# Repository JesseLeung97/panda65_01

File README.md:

# panda65_01
Kicad files for panda65_01

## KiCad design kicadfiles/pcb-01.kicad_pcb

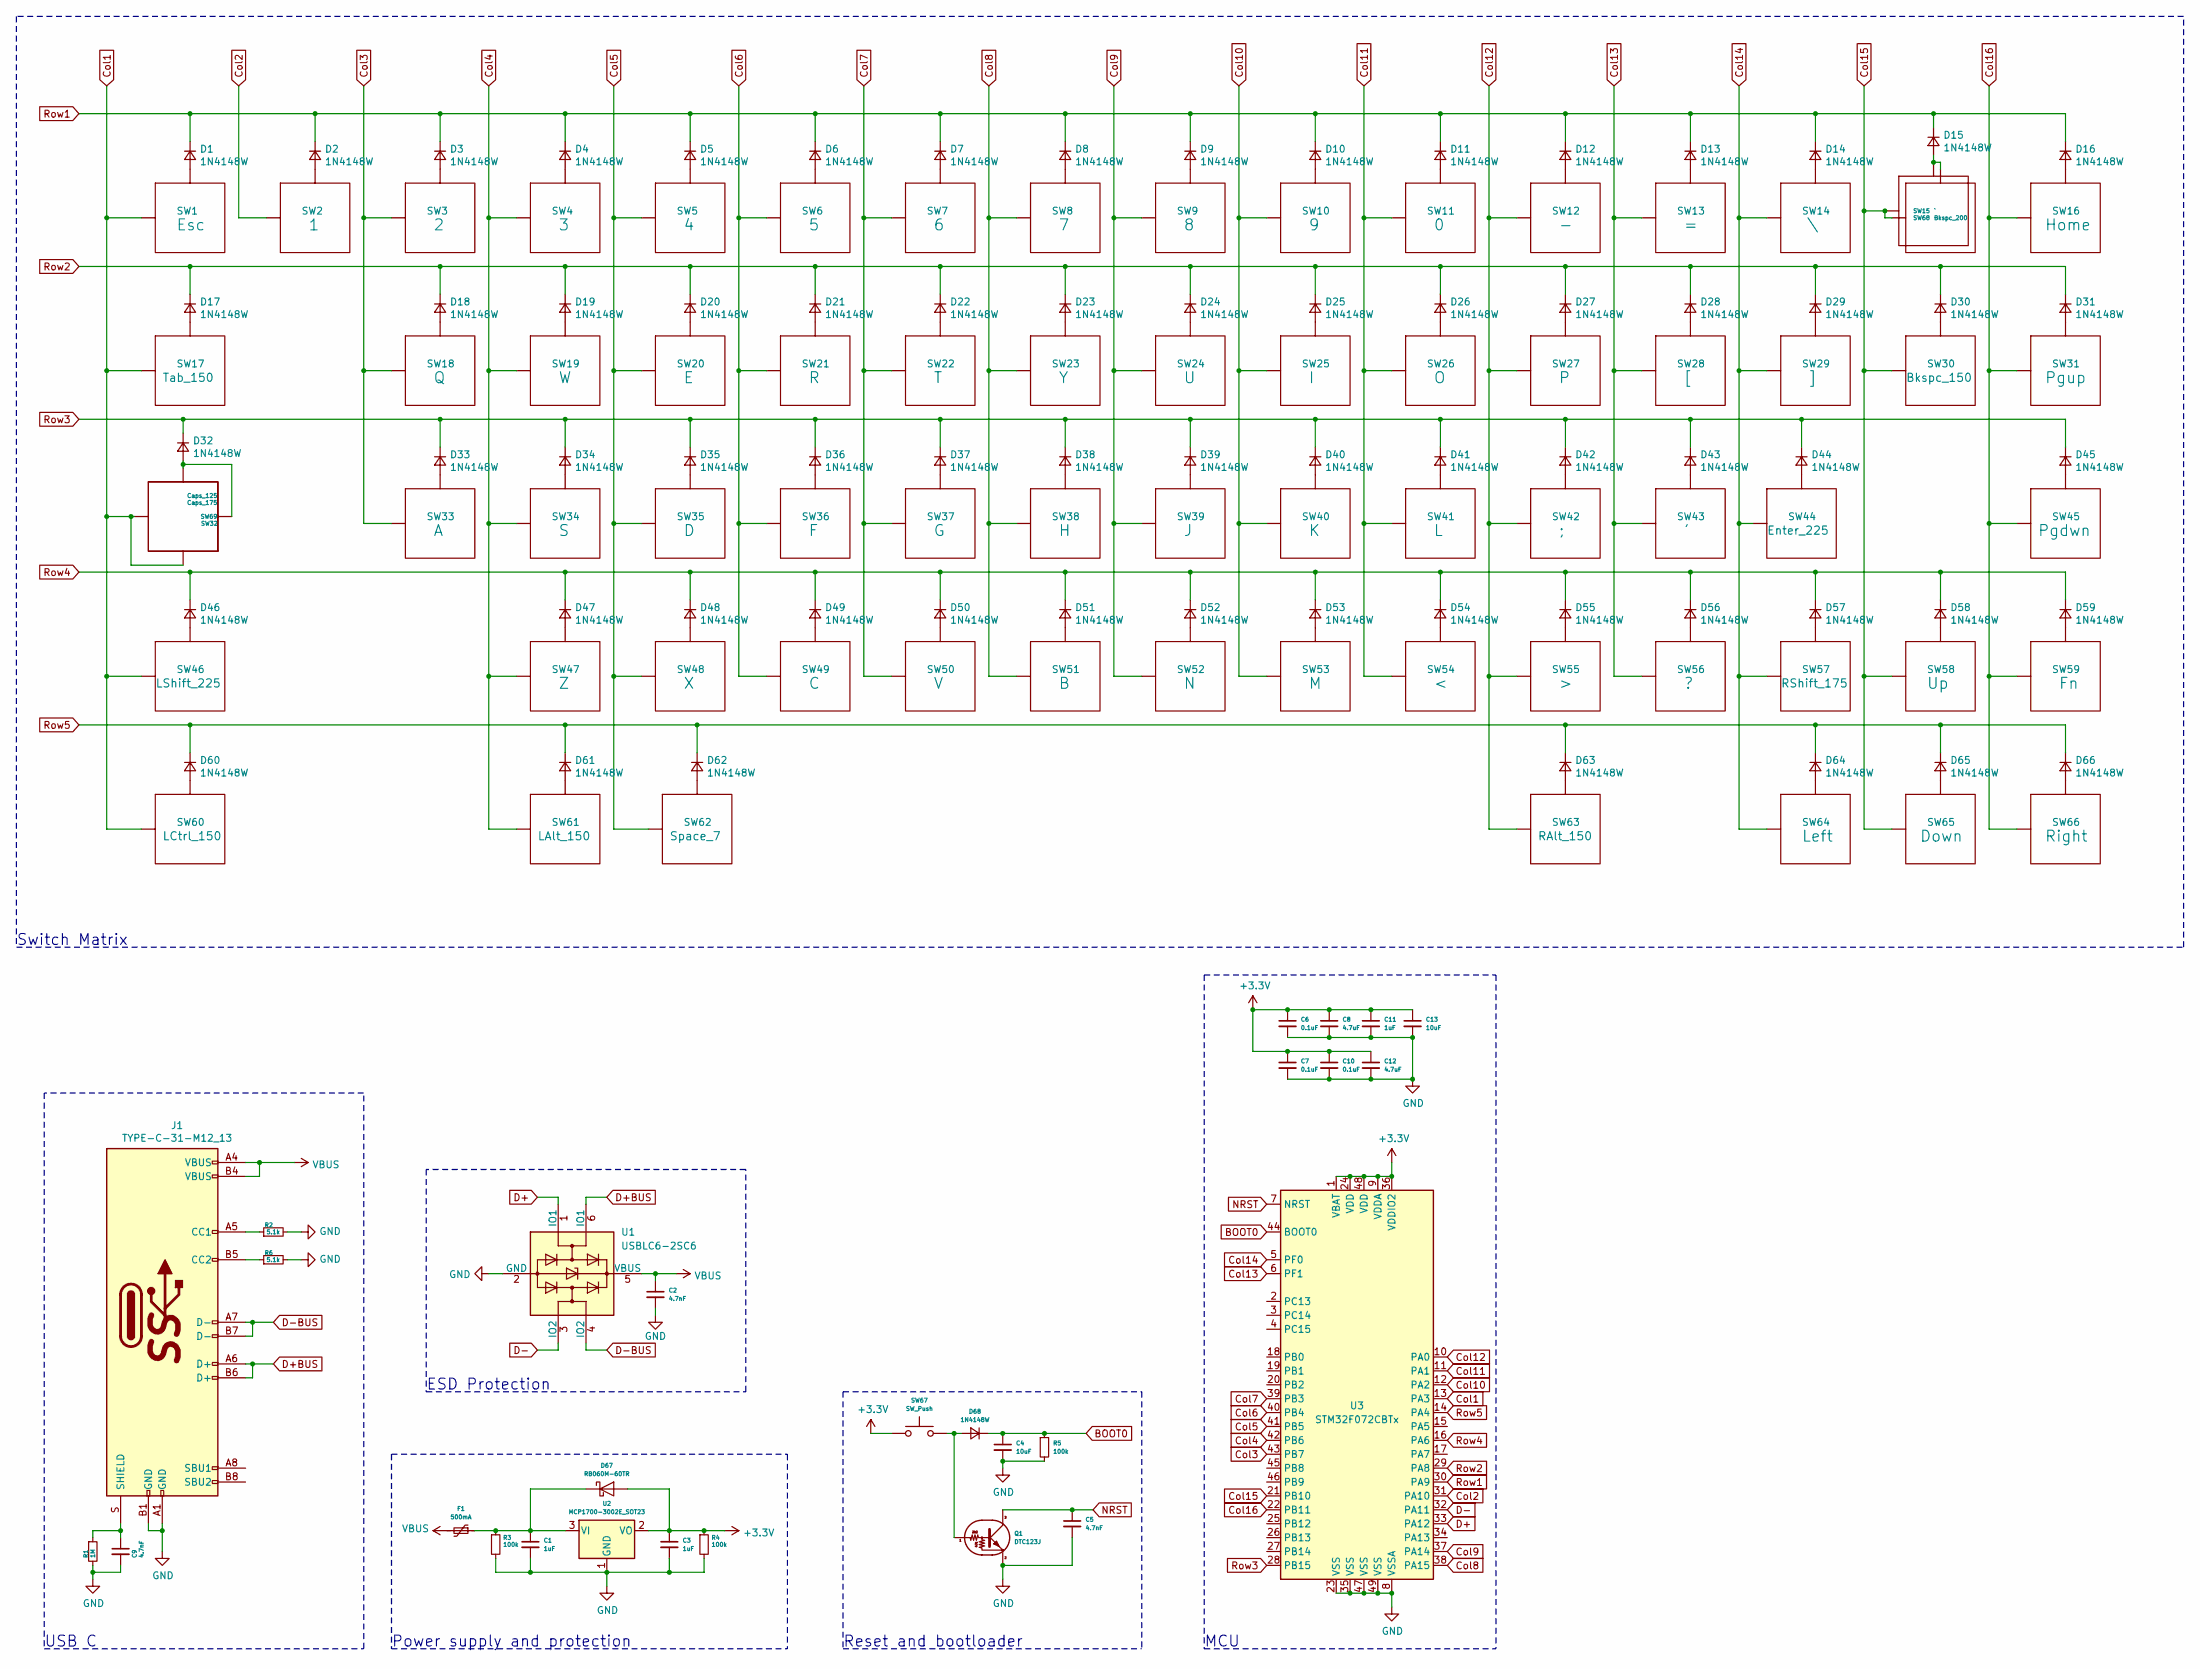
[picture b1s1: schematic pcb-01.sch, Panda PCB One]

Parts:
C1, C3, C11: 1uF; C_0603_1608Metric
C2, C5, C9: 4.7nF; C_0603_1608Metric
C4, C13: 10uF; C_0603_1608Metric
C6, C7, C10: 0.1uF; C_0603_1608Metric
C8, C12: 4.7uF; C_0603_1608Metric
D1, D2, D3, D4, D5, D6, D7, D8, D9, D10, D11, D12, D13, D14, D15, D16, D17, D18, D19, D20, D21, D22, D23, D24, D25, D26, D27, D28, D29, D30, D31, D32, D33, D34, D35, D36, D37, D38, D39, D40, D41, D42, D43, D44, D45, D46, D47, D48, D49, D50, D51, D52, D53, D54, D55, D56, D57, D58, D59, D60, D61, D62, D63, D64, D65, D66, D68: 1N4148W; D_SOD-123
D67: RB060M-60TR; D_SOD-123
F1: 500mA; Fuse_1206_3216Metric
J1: TYPE-C-31-M12_13; USB_C_Receptacle_HRO_TYPE-C-31-M-12
Q1: DTC123J; SOT-23
R1: 1M; R_0603_1608Metric
R2, R6: 5.1k; R_0603_1608Metric
R3, R4, R5: 100k; R_0603_1608Metric
SW1: Esc; MX100
SW2: 1; MX100
SW3: 2; MX100
SW4: 3; MX100
SW5: 4; MX100
SW6: 5; MX100
SW7: 6; MX100
SW8: 7; MX100
SW9: 8; MX100
SW10: 9; MX100
SW11: 0; MX100
SW12: -; MX100
SW13: =; MX100
SW14: \\; MX100
SW15: `; MX100
SW16: Home; MX100
SW17: Tab_150; MX150
SW18: Q; MX100
SW19: W; MX100
SW20: E; MX100
SW21: R; MX100
SW22: T; MX100
SW23: Y; MX100
SW24: U; MX100
SW25: I; MX100
SW26: O; MX100
SW27: P; MX100
SW28: [; MX100
SW29: ]; MX100
SW30: Bkspc_150; MX150
SW31: Pgup; MX100
SW32: Caps_175; MX175
SW33: A; MX100
SW34: S; MX100
SW35: D; MX100
SW36: F; MX100
SW37: G; MX100
SW38: H; MX100
SW39: J; MX100
SW40: K; MX100
SW41: L; MX100
SW42: ;; MX100
SW43: '; MX100
SW44: Enter_225; MX225
SW45: Pgdwn; MX100
SW46: LShift_225; MX225
SW47: Z; MX100
SW48: X; MX100
SW49: C; MX100
SW50: V; MX100
SW51: B; MX100
SW52: N; MX100
SW53: M; MX100
SW54: <; MX100
SW55: >; MX100
SW56: ?; MX100
SW57: RShift_175; MX175
SW58: Up; MX100
SW59: Fn; MX100
SW60: LCtrl_150; MX150
SW61: LAlt_150; MX150
SW62: Space_7; MX700R
SW63: RAlt_150; MX150
SW64: Left; MX100
SW65: Down; MX100
SW66: Right; MX100
SW67: SW_Push; SKQG-1155865
SW68: Bkspc_200; MX200
SW69: Caps_125; MX125
U1: USBLC6-2SC6; SOT-23-6
U2: MCP1700-3002E_SOT23; SOT-23
U3: STM32F072CBTx; QFN-48-1EP_7x7mm_P0.5mm_EP5.6x5.6mm

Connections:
+3V3: C3.1, C6.1, C7.1, C8.1, C10.1, C11.1, C12.1, C13.1, D67.2 (A), R4.1, SW67.1, U2.2 (VO), U3.1 (VBAT), U3.9 (VDDA), U3.24 (VDD), U3.36 (VDDIO2), U3.48 (VDD)
BOOT0: C4.1, D68.1 (K), R5.1, U3.44 (BOOT0)
Col1: SW1.1 (Col), SW17.1 (Col), SW32.1 (Col), SW46.1 (Col), SW60.1 (Col), SW69.2 (Row), U3.13 (PA3)
Col2: SW2.1 (Col), U3.31 (PA10)
Col3: SW3.1 (Col), SW18.1 (Col), SW33.1 (Col), U3.43 (PB7)
Col4: SW4.1 (Col), SW19.1 (Col), SW34.1 (Col), SW47.1 (Col), SW61.1 (Col), U3.42 (PB6)
Col5: SW5.1 (Col), SW20.1 (Col), SW35.1 (Col), SW48.1 (Col), SW62.1 (Col), U3.41 (PB5)
Col6: SW6.1 (Col), SW21.1 (Col), SW36.1 (Col), SW49.1 (Col), U3.40 (PB4)
Col7: SW7.1 (Col), SW22.1 (Col), SW37.1 (Col), SW50.1 (Col), U3.39 (PB3)
Col8: SW8.1 (Col), SW23.1 (Col), SW38.1 (Col), SW51.1 (Col), U3.38 (PA15)
Col9: SW9.1 (Col), SW24.1 (Col), SW39.1 (Col), SW52.1 (Col), U3.37 (PA14)
Col10: SW10.1 (Col), SW25.1 (Col), SW40.1 (Col), SW53.1 (Col), U3.12 (PA2)
Col11: SW11.1 (Col), SW26.1 (Col), SW41.1 (Col), SW54.1 (Col), U3.11 (PA1)
Col12: SW12.1 (Col), SW27.1 (Col), SW42.1 (Col), SW55.1 (Col), SW63.1 (Col), U3.10 (PA0)
Col13: SW13.1 (Col), SW28.1 (Col), SW43.1 (Col), SW56.1 (Col), U3.6 (PF1)
Col14: SW14.1 (Col), SW29.1 (Col), SW44.1 (Col), SW57.1 (Col), SW64.1 (Col), U3.5 (PF0)
Col15: SW15.1 (Col), SW30.1 (Col), SW58.1 (Col), SW65.1 (Col), SW68.1 (Col), U3.21 (PB10)
Col16: SW16.1 (Col), SW31.1 (Col), SW45.1 (Col), SW59.1 (Col), SW66.1 (Col), U3.22 (PB11)
D+: U1.1 (IO1), U3.33 (PA12)
D+BUS: J1.A6 (D+), J1.B6 (D+), U1.6 (IO1)
D-: U1.3 (IO2), U3.32 (PA11)
D-BUS: J1.A7 (D-), J1.B7 (D-), U1.4 (IO2)
GND: C1.2, C2.2, C3.2, C4.2, C5.2, C6.2, C7.2, C8.2, C9.2, C10.2, C11.2, C12.2, C13.2, J1.A1 (GND), J1.B1 (GND), Q1.2 (E), R1.2, R2.2, R3.2, R4.2, R5.2, R6.2, U1.2 (GND), U2.1 (GND), U3.8 (VSSA), U3.23 (VSS), U3.35 (VSS), U3.47 (VSS), U3.49 (VSS)
NRST: C5.1, Q1.3 (C), U3.7 (NRST)
unnamed: C1.1, D67.1 (K), F1.1, R3.1, U2.3 (VI)
unnamed: C9.1, J1.S (SHIELD), R1.1
unnamed: D1.2 (A), SW1.2 (Row)
unnamed: D2.2 (A), SW2.2 (Row)
unnamed: D3.2 (A), SW3.2 (Row)
unnamed: D4.2 (A), SW4.2 (Row)
unnamed: D5.2 (A), SW5.2 (Row)
unnamed: D6.2 (A), SW6.2 (Row)
unnamed: D7.2 (A), SW7.2 (Row)
unnamed: D8.2 (A), SW8.2 (Row)
unnamed: D9.2 (A), SW9.2 (Row)
unnamed: D10.2 (A), SW10.2 (Row)
unnamed: D11.2 (A), SW11.2 (Row)
unnamed: D12.2 (A), SW12.2 (Row)
unnamed: D13.2 (A), SW13.2 (Row)
unnamed: D14.2 (A), SW14.2 (Row)
unnamed: D15.2 (A), SW15.2 (Row), SW68.2 (Row)
unnamed: D16.2 (A), SW16.2 (Row)
unnamed: D17.2 (A), SW17.2 (Row)
unnamed: D18.2 (A), SW18.2 (Row)
unnamed: D19.2 (A), SW19.2 (Row)
unnamed: D20.2 (A), SW20.2 (Row)
unnamed: D21.2 (A), SW21.2 (Row)
unnamed: D22.2 (A), SW22.2 (Row)
unnamed: D23.2 (A), SW23.2 (Row)
unnamed: D24.2 (A), SW24.2 (Row)
unnamed: D25.2 (A), SW25.2 (Row)
unnamed: D26.2 (A), SW26.2 (Row)
unnamed: D27.2 (A), SW27.2 (Row)
unnamed: D28.2 (A), SW28.2 (Row)
unnamed: D29.2 (A), SW29.2 (Row)
unnamed: D30.2 (A), SW30.2 (Row)
unnamed: D31.2 (A), SW31.2 (Row)
unnamed: D32.2 (A), SW32.2 (Row), SW69.1 (Col)
unnamed: D33.2 (A), SW33.2 (Row)
unnamed: D34.2 (A), SW34.2 (Row)
unnamed: D35.2 (A), SW35.2 (Row)
unnamed: D36.2 (A), SW36.2 (Row)
unnamed: D37.2 (A), SW37.2 (Row)
unnamed: D38.2 (A), SW38.2 (Row)
unnamed: D39.2 (A), SW39.2 (Row)
unnamed: D40.2 (A), SW40.2 (Row)
unnamed: D41.2 (A), SW41.2 (Row)
unnamed: D42.2 (A), SW42.2 (Row)
unnamed: D43.2 (A), SW43.2 (Row)
unnamed: D44.2 (A), SW44.2 (Row)
unnamed: D45.2 (A), SW45.2 (Row)
unnamed: D46.2 (A), SW46.2 (Row)
unnamed: D47.2 (A), SW47.2 (Row)
unnamed: D48.2 (A), SW48.2 (Row)
unnamed: D49.2 (A), SW49.2 (Row)
unnamed: D50.2 (A), SW50.2 (Row)
unnamed: D51.2 (A), SW51.2 (Row)
unnamed: D52.2 (A), SW52.2 (Row)
unnamed: D53.2 (A), SW53.2 (Row)
unnamed: D54.2 (A), SW54.2 (Row)
unnamed: D55.2 (A), SW55.2 (Row)
unnamed: D56.2 (A), SW56.2 (Row)
unnamed: D57.2 (A), SW57.2 (Row)
unnamed: D58.2 (A), SW58.2 (Row)
unnamed: D59.2 (A), SW59.2 (Row)
unnamed: D60.2 (A), SW60.2 (Row)
unnamed: D61.2 (A), SW61.2 (Row)
unnamed: D62.2 (A), SW62.2 (Row)
unnamed: D63.2 (A), SW63.2 (Row)
unnamed: D64.2 (A), SW64.2 (Row)
unnamed: D65.2 (A), SW65.2 (Row)
unnamed: D66.2 (A), SW66.2 (Row)
unnamed: D68.2 (A), Q1.1 (B), SW67.2
unnamed: J1.A5 (CC1), R2.1
unnamed: J1.B5 (CC2), R6.1
Row1: D1.1 (K), D2.1 (K), D3.1 (K), D4.1 (K), D5.1 (K), D6.1 (K), D7.1 (K), D8.1 (K), D9.1 (K), D10.1 (K), D11.1 (K), D12.1 (K), D13.1 (K), D14.1 (K), D15.1 (K), D16.1 (K), U3.30 (PA9)
Row2: D17.1 (K), D18.1 (K), D19.1 (K), D20.1 (K), D21.1 (K), D22.1 (K), D23.1 (K), D24.1 (K), D25.1 (K), D26.1 (K), D27.1 (K), D28.1 (K), D29.1 (K), D30.1 (K), D31.1 (K), U3.29 (PA8)
Row3: D32.1 (K), D33.1 (K), D34.1 (K), D35.1 (K), D36.1 (K), D37.1 (K), D38.1 (K), D39.1 (K), D40.1 (K), D41.1 (K), D42.1 (K), D43.1 (K), D44.1 (K), D45.1 (K), U3.28 (PB15)
Row4: D46.1 (K), D47.1 (K), D48.1 (K), D49.1 (K), D50.1 (K), D51.1 (K), D52.1 (K), D53.1 (K), D54.1 (K), D55.1 (K), D56.1 (K), D57.1 (K), D58.1 (K), D59.1 (K), U3.16 (PA6)
Row5: D60.1 (K), D61.1 (K), D62.1 (K), D63.1 (K), D64.1 (K), D65.1 (K), D66.1 (K), U3.14 (PA4)
VBUS: C2.1, F1.2, J1.A4 (VBUS), J1.B4 (VBUS), U1.5 (VBUS)

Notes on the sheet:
Switch Matrix
USB C
ESD Protection
Reset and bootloader
MCU
Power supply and protection

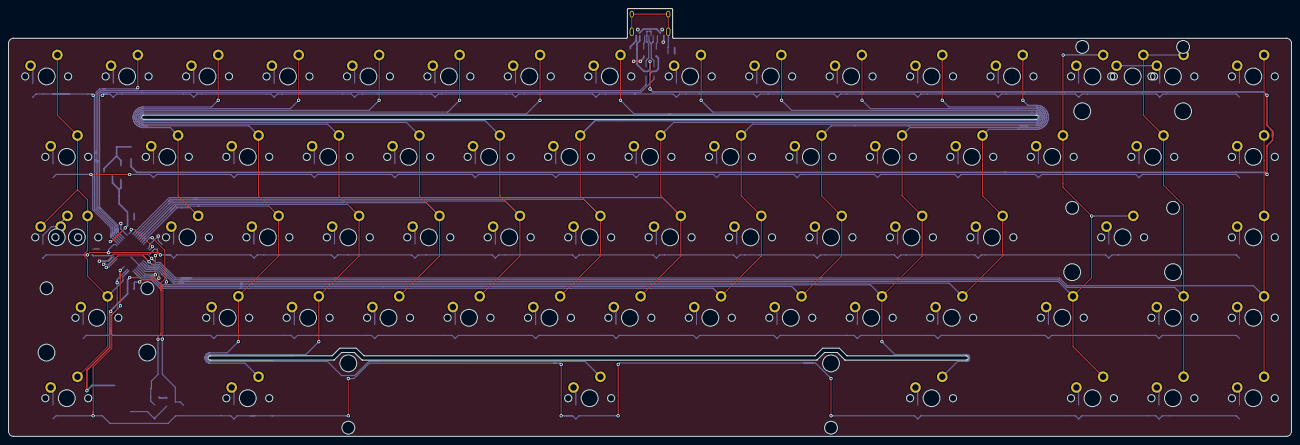
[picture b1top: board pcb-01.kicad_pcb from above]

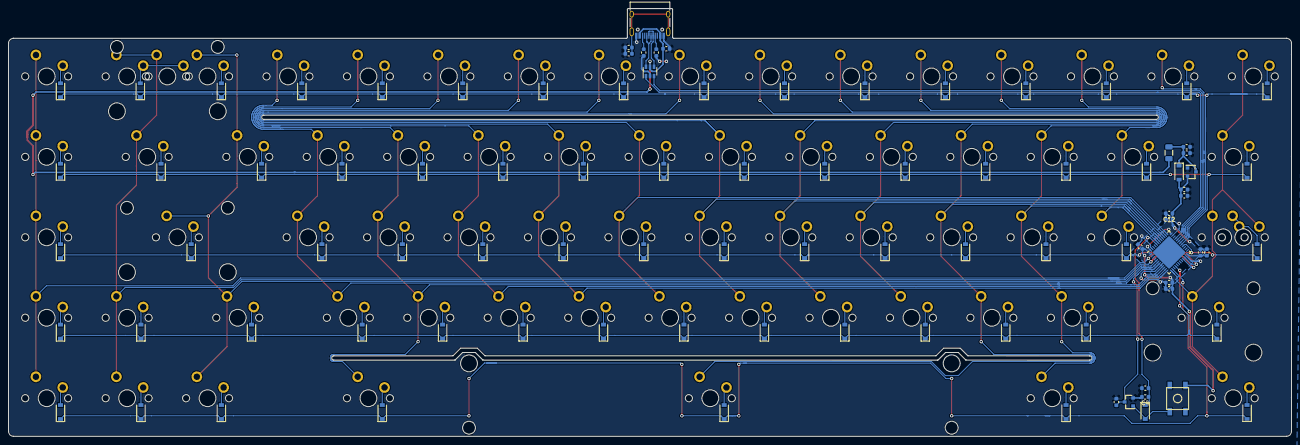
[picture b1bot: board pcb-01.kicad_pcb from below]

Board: 2 copper layers, 303.8 x 101.3 mm, 162 parts (162 on the bottom side), 101 nets.

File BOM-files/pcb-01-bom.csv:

Comment,Designator,Footprint,LCSC
1uF,"C1,C3,C11",Capacitor_SMD:C_0603_1608Metric,C15849
10uF,"C4,C13",Capacitor_SMD:C_0603_1608Metric,C19702
0.1uF,"C6,C7,C10",Capacitor_SMD:C_0603_1608Metric,C14663
4.7uF,"C8,C12",Capacitor_SMD:C_0603_1608Metric,C19666
4.7nF,"C2,C5,C9",Capacitor_SMD:C_0603_1608Metric,C53987
1N4148W,"D1,D2,D3,D4,D5,D6,D7,D8,D9,D10,D11,D12,D13,D14,D15,D16,D17,D18,D19,D20,D21,D22,D23,D24,D25,D26,D27,D28,D29,D30,D31,D32,D33,D34,D35,D36,D37,D38,D39,D40,D41,D42,D43,D44,D45,D46,D47,D48,D49,D50,D51,D52,D53,D54,D55,D56,D57,D58,D59,D60,D61,D62,D63,D64,D65,D66,D68",Diode_SMD:D_SOD-123,C81598
RB060M-60TR,D67,Diode_SMD:D_SOD-123,C8598
DTC123J,Q1,Package_TO_SOT_SMD:SOT-23,C111724
1M,R1,Resistor_SMD:R_0603_1608Metric,C22935
5.1k,"R2,R6",Resistor_SMD:R_0603_1608Metric,C23186
100k,"R3,R4,R5",Resistor_SMD:R_0603_1608Metric,C25803
SW_Push,SW67,random-keyboard-parts:SKQG-1155865,C318884
USBLC6-2SC6,U1,Package_TO_SOT_SMD:SOT-23-6,C7519
MCP1700-3002E_SOT23,U2,Package_TO_SOT_SMD:SOT-23,C5446
STM32F072CBTx,U3,Package_DFN_QFN:QFN-48-1EP_7x7mm_P0.5mm_EP5.6x5.6mm,C92504

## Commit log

2020-08-11 changed repository to match name
2020-08-11 Create license
2020-08-12 updated pcb graphics
2020-08-13 arranged files and updated gerbers
2020-08-13 moved license to main folder
2020-08-16 added polyfuse and updated routing
